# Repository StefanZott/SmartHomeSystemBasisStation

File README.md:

# SmartHomeSystemBasisStation

## Kurzbeschreibung

SmartHome-Basisstation auf Basis des **ESP32-S3** mit eigener Platine, ESP-IDF-Firmware und Web-Oberfläche zur WLAN-Konfiguration und Gerätediagnose. Das Repository bündelt Hardware (KiCad), Firmware und SPIFFS-Web-Assets in einem Projekt.

## Architektur-Überblick

| Pfad | Inhalt |
|------|--------|
| `main/` | Firmware (ESP-IDF), Einstieg `main.c` |
| `spiffs/` | Web-UI (HTML, CSS, JS) → SPIFFS-Image |
| `pcb/` | KiCad-Schaltplan und Layout der Basisstation |
| `docs/` | Projektdokumentation und Anwenderdoku |

Stückliste und Pinout: [docs/project/hardware.md](docs/project/hardware.md)

## Toolchain

- **Firmware:** [ESP-IDF](https://docs.espressif.com/projects/esp-idf/) **v5.5.2** für ESP32-S3, Build über `idf.py`
- **IDE:** VS Code mit ESP-IDF-Erweiterung; optional Dev Container (`.devcontainer/`)
- **Hardware:** KiCad 8/9 — Projekt unter `pcb/BasisStation/`

## Deep Dive

Technische Architektur, Module, Startablauf und Verzeichnisstruktur:

→ [docs/project/architecture.md](docs/project/architecture.md)

Weitere Themen: [Kommunikation](docs/project/communication.md) · [Sicherheit](docs/project/security.md) · [Speicher-Layout](docs/project/memory_map.md)

## Deployment

Build, Flash und Monitor (Kurzfassung):

```text
idf.py set-target esp32s3
idf.py build
idf.py flash monitor
```

Ausführliche Anleitung, Partitionierung und Voraussetzungen:

→ [docs/project/architecture.md#deployment](docs/project/architecture.md#deployment)

## Release & Tags

Aktuelle Firmware-Version: siehe Datei [`version`](version) (Format `X.XX.XXX`, derzeit `0.00.001`).

| Tag (Beispiel) | Bedeutung |
|----------------|-----------|
| `v0.00.001` | Veröffentlichte bzw. testbare Firmware-Version |
| `release` | Marker für den aktuellen Release-Stand im Repository |

Kundenspezifische Builds: `v0.00.005-kundexyz`. Details: [docs/userdoc/git_guidelines.md](docs/userdoc/git_guidelines.md).

Agenten-Regeln und Workflow: [CLAUDE.md](CLAUDE.md)

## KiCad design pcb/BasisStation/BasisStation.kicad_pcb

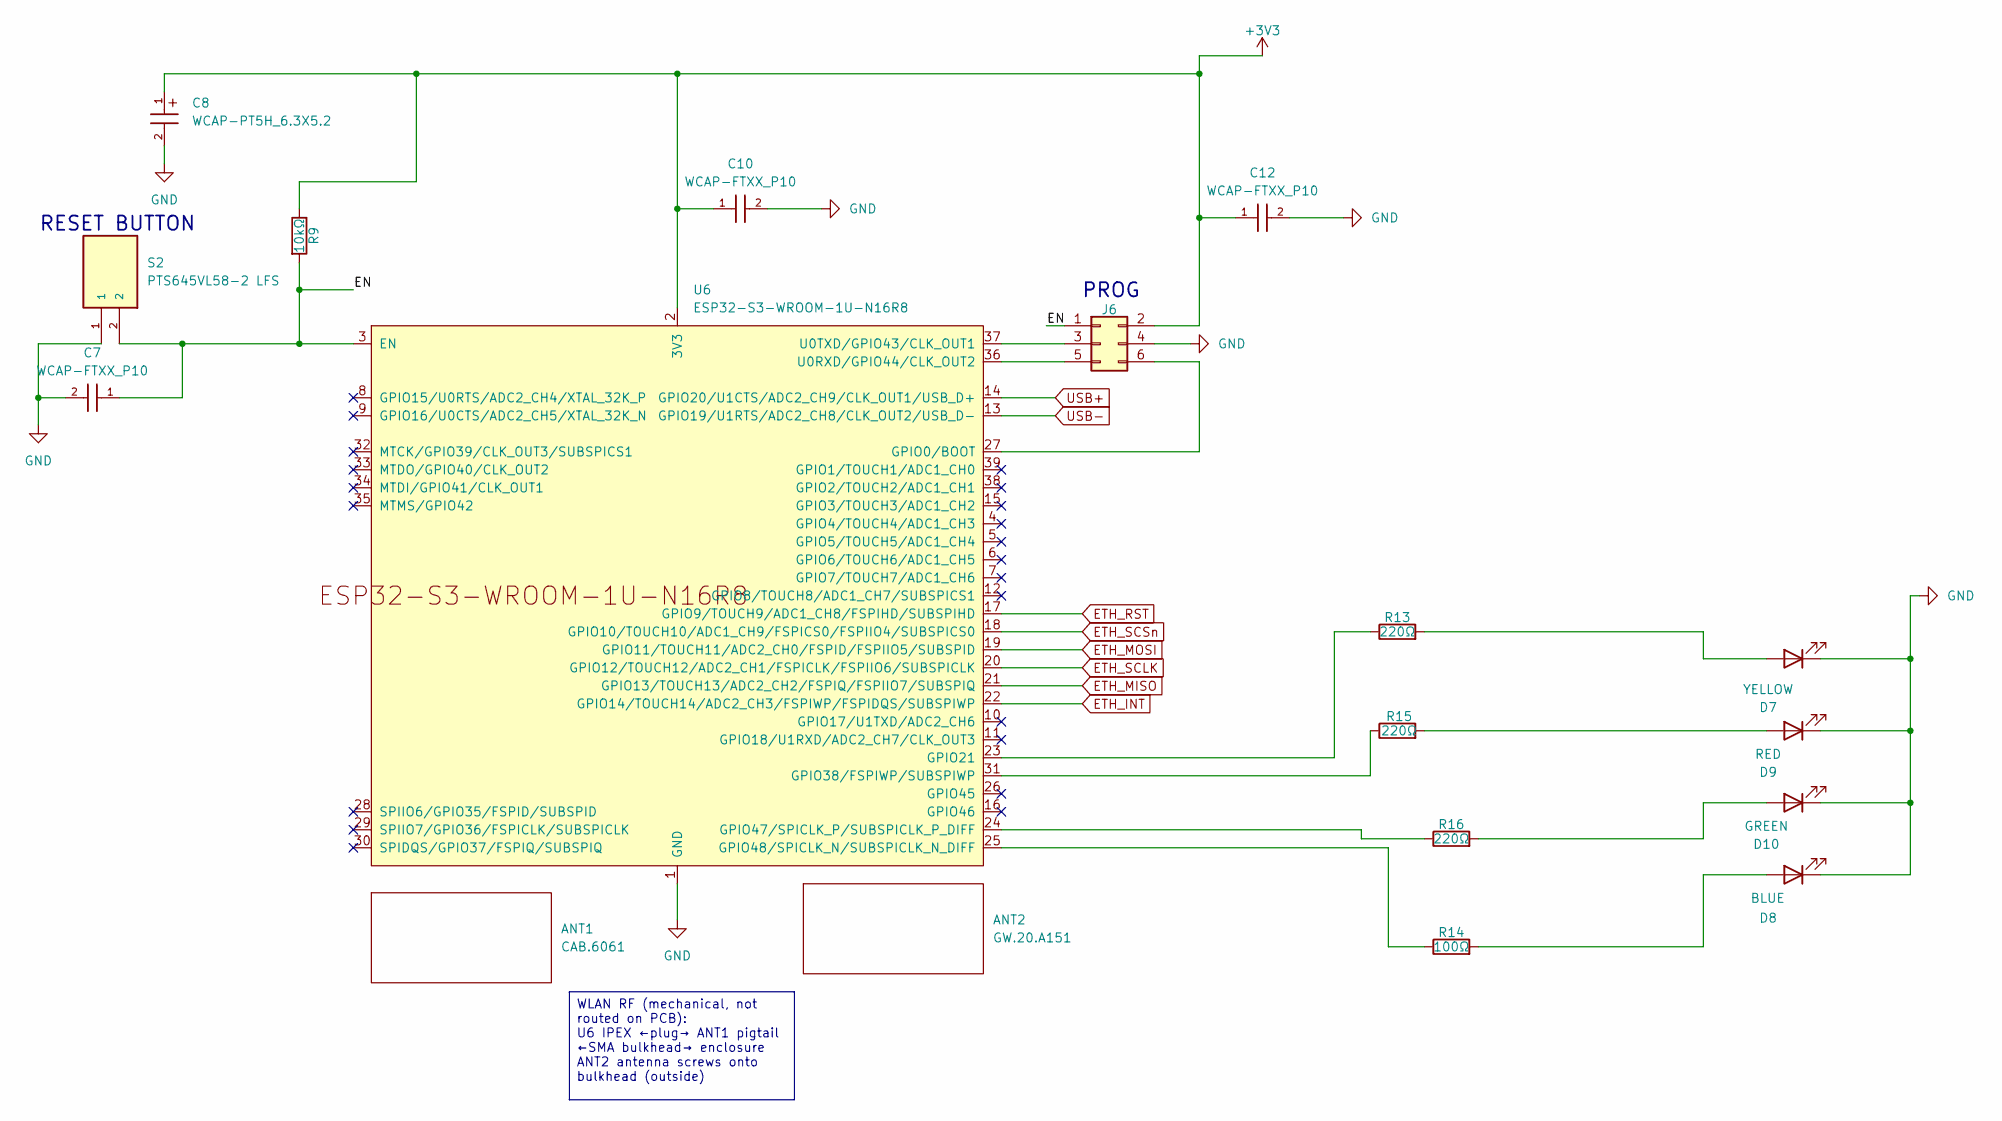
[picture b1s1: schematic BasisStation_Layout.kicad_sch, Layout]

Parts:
ANT1: CAB.6061; Manufacturer_Part_Number CAB.6061; Mouser Part Number 960-CAB.6061
ANT2: GW.20.A151; Manufacturer_Part_Number GW.20.A151; Mouser Part Number 960-GW.20.A151
C7, C10, C12: WCAP-FTXX_P10; WCAP-FTXX_P10L13W7H13
C8: WCAP-PT5H_6.3X5.2; WCAP-PT5H_6.3X5.2_DXL_
D7: YELLOW; LED_D3.0mm_Horizontal_O1.27mm_Z2.0mm
D8: BLUE; LED_D3.0mm_Horizontal_O1.27mm_Z2.0mm; Manufacturer_Part_Number 151033BS03000; Mouser Part Number 710-151033BS03000
D9: RED; LED_D3.0mm_Horizontal_O1.27mm_Z2.0mm; Manufacturer_Part_Number 151033RS03000; Mouser Part Number 710-151033RS03000
D10: GREEN; LED_D3.0mm_Horizontal_O1.27mm_Z2.0mm; Manufacturer_Part_Number 151031VS06000; Mouser Part Number 710-151031VS06000
J6: 61200621621; Manufacturer_Part_Number 61200621621; Mouser Part Number 710-61200621621
R9: 10kΩ; R_0805_2012Metric; Manufacturer_Part_Number RC0805FR-0710KL; Mouser Part Number 603-RC0805FR-0710KL
R13, R15, R16: 220Ω; R_0805_2012Metric; Manufacturer_Part_Number RC0805FR-07220RL; Mouser Part Number 603-RC0805FR-07220RL
R14: 100Ω; R_0805_2012Metric; Manufacturer_Part_Number RC0805FR-07100RL; Mouser Part Number 603-RC0805FR-07100RL
S2: PTS645VL58-2 LFS; SW_Tactile_SPST_Angled_PTS645Vx58-2LFS; MOUSER_PART_NUMBER 611-PTS645VL582
U6: ESP32-S3-WROOM-1U-N16R8; ESP32-S3-WROOM-1U; Mouser Part Number 356-ESP32S3WM1UN16R8

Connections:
+3V3: C8.1, C10.1, C12.1, J6.2, R9.1, U6.2 (3V3); also elsewhere on the board
/Layout/EN: C7.1, J6.1, R9.2, S2.2, U6.3 (EN)
ETH_INT: U6.22 (GPIO14/TOUCH14/ADC2_CH3/FSPIWP/FSPIDQS/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); also elsewhere on the board
ETH_MISO: U6.21 (GPIO13/TOUCH13/ADC2_CH2/FSPIQ/FSPIIO7/S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); also elsewhere on the board
ETH_MOSI: U6.19 (GPIO11/TOUCH11/ADC2_CH0/FSPID/FSPIIO5/S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); also elsewhere on the board
ETH_RST: U6.17 (GPIO9/TOUCH9/ADC1_CH8/FSPIHD/SUBSPIHD); also elsewhere on the board
ETH_SCLK: U6.20 (GPIO12/TOUCH12/ADC2_CH1/FSPICLK/FSPIIO6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); also elsewhere on the board
ETH_SCSn: U6.18 (GPIO10/TOUCH10/ADC1_CH9/FSPICS0/FSPIIO4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); also elsewhere on the board
GND: C7.2, C8.2, C10.2, C12.2, D7.1 (K), D8.1 (K), D9.1 (K), D10.1 (K), J6.4, S2.1, U6.1 (GND), U6.40 (GND), U6.41 (GND); also elsewhere on the board
unnamed: D7.2 (A), R13.2
unnamed: D8.2 (A), R14.2
unnamed: D9.2 (A), R15.2
unnamed: D10.2 (A), R16.2
unnamed: J6.3, U6.37 (U0TXD/GPIO43/CLK_OUT1)
unnamed: J6.5, U6.36 (U0RXD/GPIO44/CLK_OUT2)
unnamed: J6.6, U6.27 (GPIO0/BOOT)
unnamed: R13.1, U6.23 (GPIO21)
unnamed: R15.1, U6.31 (GPIO38/FSPIWP/SUBSPIWP)
unnamed: R16.1, U6.24 (GPIO47/SPICLK_P/SUBSPICLK_P_DIFF)
unnamed: R14.1, U6.25 (GPIO48/SPICLK_N/SUBSPICLK_N_DIFF)
USB+: U6.14 (GPIO20/U1CTS/ADC2_CH9/CLK_OUT1/USB_D+); also elsewhere on the board
USB-: U6.13 (GPIO19/U1RTS/ADC2_CH8/CLK_OUT2/USB_D-); also elsewhere on the board

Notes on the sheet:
RESET BUTTON
PROG
WLAN RF (mechanical, not routed on PCB): U6 IPEX ←plug→ ANT1 pigtail ←SMA bulkhead→ enclosure ANT2 antenna screws onto bulkhead (outside)

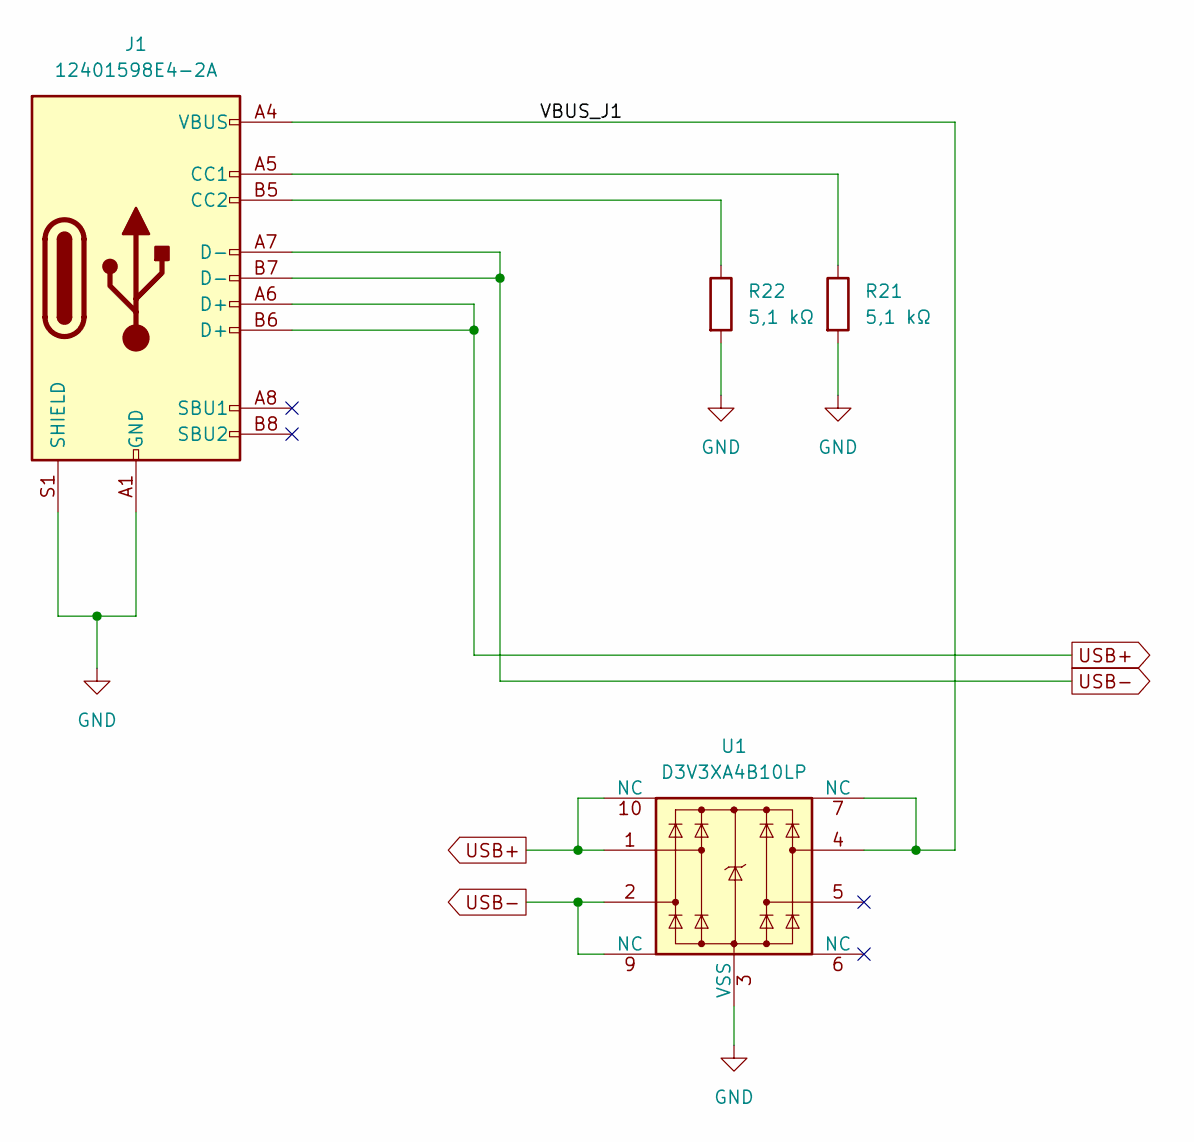
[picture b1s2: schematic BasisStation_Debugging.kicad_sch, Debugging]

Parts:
J1: 12401598E4-2A; USB_C_Receptacle_Amphenol_12401598E4-2A; Manufacturer_Part_Number 12401598E4#2A; Mouser Part Number 523-12401598E4#2A
R21, R22: 5,1 kΩ; R_0805_2012Metric; Manufacturer_Part_Number RC0805FR-075K1L; Mouser Part Number 603-RC0805FR-075K1L
U1: D3V3XA4B10LP; Diodes_UDFN-10_1x2.5mm_P0.5mm; Manufacturer_Part_Number D3V3XA4B10LP-7; Mouser Part Number 621-D3V3XA4B10LP-7

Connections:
/Debugging/VBUS_J1: J1.A4 (VBUS), J1.A9 (VBUS), J1.B4 (VBUS), J1.B9 (VBUS), U1.4, U1.7 (NC)
GND: J1.A1 (GND), J1.A12 (GND), J1.B1 (GND), J1.B12 (GND), J1.S1 (SHIELD), R21.2, R22.2, U1.3 (VSS), U1.8 (VSS); also elsewhere on the board
unnamed: J1.A5 (CC1), R21.1
unnamed: J1.B5 (CC2), R22.1
USB+: J1.A6 (D+), J1.B6 (D+), U1.1, U1.10 (NC); also elsewhere on the board
USB-: J1.A7 (D-), J1.B7 (D-), U1.2, U1.9 (NC); also elsewhere on the board

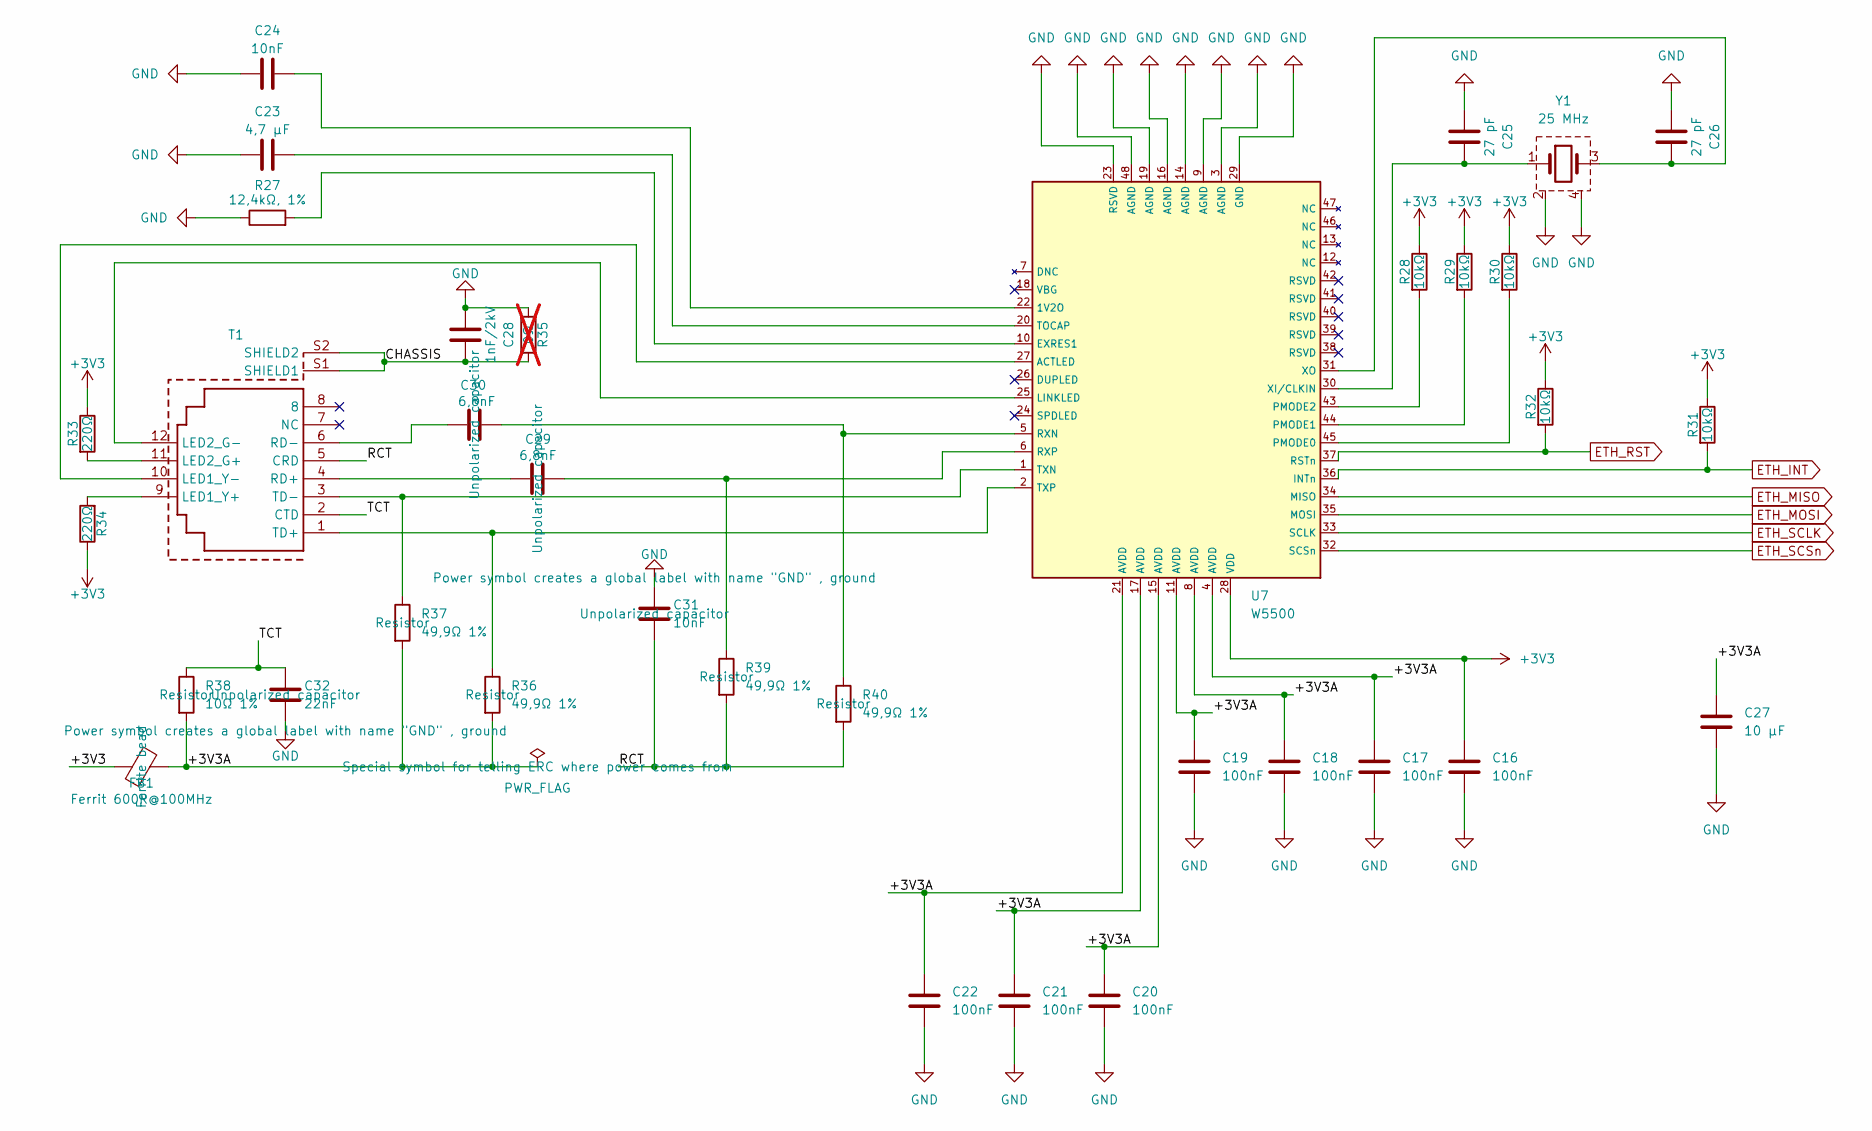
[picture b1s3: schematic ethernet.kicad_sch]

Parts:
C16, C17, C18, C19, C20, C21, C22: 100nF; C_0805_2012Metric; Manufacturer_Part_Number CC0805KRX7R9BB104; Mouser Part Number 603-CC805KRX7R9BB104
C23: 4,7 µF; C_0805_2012Metric; Manufacturer_Part_Number CL21A475KAQNNNE; Mouser Part Number 187-CL21A475KAQNNNE
C24, C31: 10nF; C_0805_2012Metric; Manufacturer_Part_Number CC0805KRX7R9BB103; Mouser Part Number 603-CC805KRX7R9BB103
C25, C26: 27 pF; C_0805_2012Metric; Manufacturer_Part_Number CC0805JRNPO9BN270; Mouser Part Number 603-CC805JRNPO9BN270
C27: 10 µF; C_0805_2012Metric; Manufacturer_Part_Number CL21B106KOQNNNE; Mouser Part Number 187-CL21B106KOQNNNE
C28: 1nF/2kV; C_1206_3216Metric; Manufacturer_Part_Number C1206C102KGRACTU; Mouser Part Number 80-C1206C102KGR
C29, C30: 6,8nF; C_0805_2012Metric; Manufacturer_Part_Number CC0805KRX7R9BB682; Mouser Part Number 603-CC805KRX7R9BB682
C32: 22nF; C_0805_2012Metric; Manufacturer_Part_Number CL21B223KBANNNC; Mouser Part Number 187-CL21B223KBANNNC
FB1: Ferrit 600R@100MHz; L_0805_2012Metric; Manufacturer_Part_Number BLM21PG601SN1D; Mouser Part Number 81-BLM21PG601SN1D
R27: 12,4kΩ, 1%; R_0805_2012Metric; Manufacturer_Part_Number RC0805FR-0712K4L; Mouser Part Number 603-RC0805FR-0712K4L
R28, R29, R30, R31, R32: 10kΩ; R_0805_2012Metric; Manufacturer_Part_Number RC0805FR-0710KL; Mouser Part Number 603-RC0805FR-0710KL
R33, R34: 220Ω; R_0805_2012Metric; Manufacturer_Part_Number RC0805FR-07220RL; Mouser Part Number 603-RC0805FR-07220RL
R35: 0Ω; R_0805_2012Metric; Manufacturer_Part_Number RC0805JR-070RL; Mouser Part Number 603-RC0805JR-070RL; not fitted
R36, R37, R39, R40: 49,9Ω 1%; R_0805_2012Metric; Manufacturer_Part_Number RC0805FR-0749R9L; Mouser Part Number 603-RC0805FR-0749R9L
R38: 10Ω 1%; R_0805_2012Metric; Manufacturer_Part_Number RC0805FR-0710RL; Mouser Part Number 603-RC0805FR-0710RL
T1: 7499011121A; T_Wurth_WE-RJ45LAN_7499011121A; Part Number 7499011121A; Mouser Part Number 710-7499011121A
U7: W5500; 48LQFP_W5500_WIZ; Manufacturer_Part_Number W5500
Y1: 25 MHz; Y_Wurth_WE-XTAL_Quartz-CFPX-104; Part Number 830059532; Mouser Part Number 710-830059532

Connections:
+3V3: C16.1, FB1.1, R28.1, R29.1, R30.1, R31.1, R32.1, R33.1, R34.1, U7.28 (VDD); also elsewhere on the board
/Ethernet/+3V3A: C17.1, C18.1, C19.1, C20.1, C21.1, C22.1, C27.1, FB1.2, R36.2, R37.2, R38.2, U7.4 (AVDD), U7.8 (AVDD), U7.11 (AVDD), U7.15 (AVDD), U7.17 (AVDD), U7.21 (AVDD)
/Ethernet/CHASSIS: C28.2, R35.1, T1.S1 (SHIELD1), T1.S2 (SHIELD2)
/Ethernet/RCT: C31.2, R39.2, R40.2, T1.5 (CRD)
/Ethernet/TCT: C32.1, R38.1, T1.2 (CTD)
ETH_INT: R31.2, U7.36 (INTn); also elsewhere on the board
ETH_MISO: U7.34 (MISO); also elsewhere on the board
ETH_MOSI: U7.35 (MOSI); also elsewhere on the board
ETH_RST: R32.2, U7.37 (RSTn); also elsewhere on the board
ETH_SCLK: U7.33 (SCLK); also elsewhere on the board
ETH_SCSn: U7.32 (SCSn); also elsewhere on the board
GND: C16.2, C17.2, C18.2, C19.2, C20.2, C21.2, C22.2, C23.1, C24.1, C25.1, C26.1, C27.2, C28.1, C31.1, C32.2, R27.1, R35.2, U7.3 (AGND), U7.9 (AGND), U7.14 (AGND), U7.16 (AGND), U7.19 (AGND), U7.23 (RSVD), U7.29 (GND), U7.48 (AGND), Y1.2 (GND), Y1.4 (GND1); also elsewhere on the board
unnamed: R34.2, T1.9 (LED1_Y+)
unnamed: T1.10 (LED1_Y-), U7.27 (ACTLED)
unnamed: R33.2, T1.11 (LED2_G+)
unnamed: T1.12 (LED2_G-), U7.25 (LINKLED)
unnamed: C29.1, T1.4 (RD+)
unnamed: C30.1, T1.6 (RD-)
unnamed: R36.1, T1.1 (TD+), U7.2 (TXP)
unnamed: R37.1, T1.3 (TD-), U7.1 (TXN)
unnamed: C24.2, U7.22 (1V2O)
unnamed: R27.2, U7.10 (EXRES1)
unnamed: R30.2, U7.45 (PMODE0)
unnamed: R29.2, U7.44 (PMODE1)
unnamed: R28.2, U7.43 (PMODE2)
unnamed: C30.2, R40.1, U7.5 (RXN)
unnamed: C29.2, R39.1, U7.6 (RXP)
unnamed: C23.2, U7.20 (TOCAP)
unnamed: C25.2, U7.30 (XI/CLKIN), Y1.1
unnamed: C26.2, U7.31 (XO), Y1.3

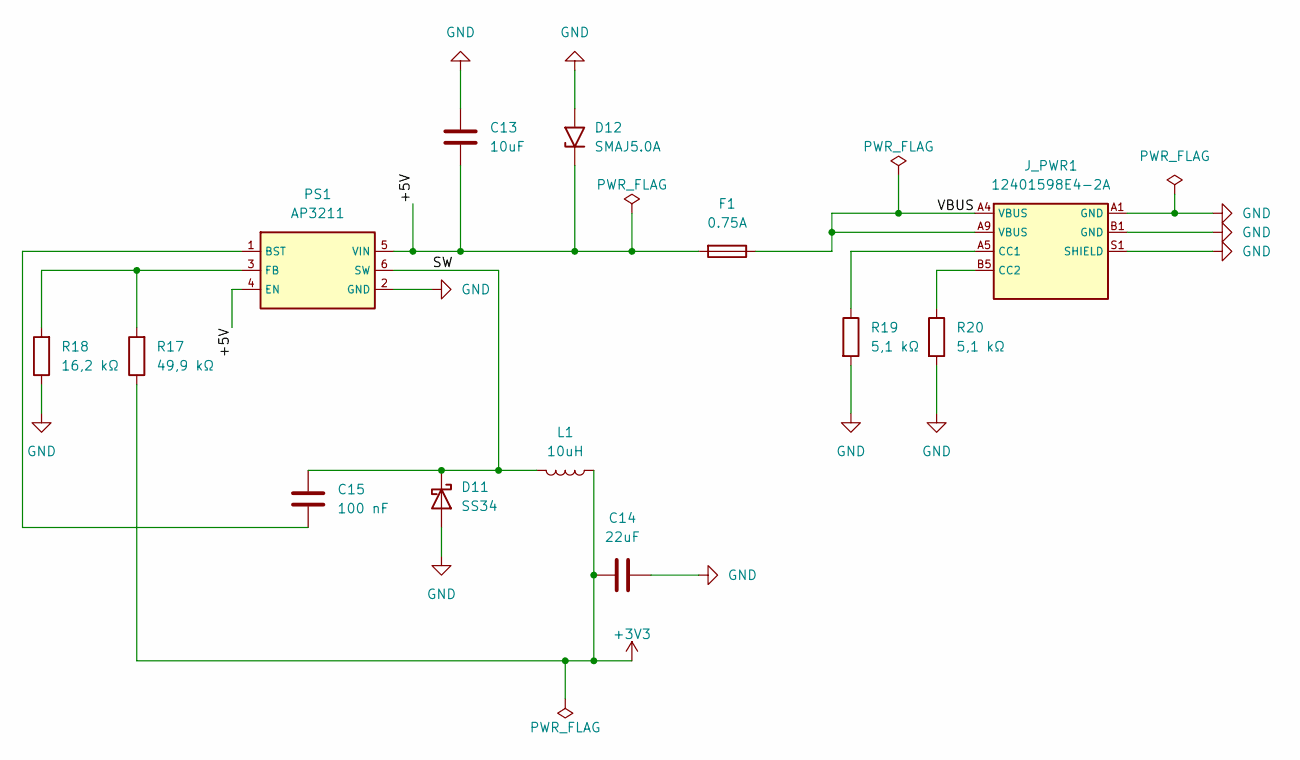
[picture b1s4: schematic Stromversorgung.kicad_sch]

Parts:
C13: 10uF; C_0805_2012Metric; Manufacturer_Part_Number CL21B106KOQNNNE; Mouser Part Number 187-CL21B106KOQNNNE
C14: 22uF; C_0805_2012Metric; Manufacturer_Part_Number CL21A226MOQNNNE; Mouser Part Number 187-CL21A226MOQNNNE
C15: 100 nF; C_0805_2012Metric; Manufacturer_Part_Number CC0805KRX7R9BB104; Mouser Part Number 603-CC805KRX7R9BB104
D11: SS34; D_SMA; Manufacturer_Part_Number SS34-HF; Mouser Part Number 750-SS34-HF
D12: SMAJ5.0A; D_SMA; Manufacturer_Part_Number SMAJ5.0A; Mouser Part Number 576-SMAJ5.0A
F1: 0.75A; Fuse_1206_3216Metric; Manufacturer_Part_Number 1206L075/16WR; Mouser Part Number 576-1206L075/16WR
J_PWR1: 12401598E4-2A; USB_C_Receptacle_Amphenol_12401598E4-2A; Manufacturer_Part_Number 12401598E4#2A; Mouser Part Number 523-12401598E4#2A
L1: 10uH; L_Bourns_SRN6045TA; Manufacturer_Part_Number SRN6045TA-100M; Mouser Part Number 652-SRN6045TA-100M
PS1: AP3211; MP2359DJ; Manufacturer_Part_Number AP3211KTR-G1; Mouser Part Number 621-AP3211KTR-G1
R17: 49,9 kΩ; R_0805_2012Metric; Manufacturer_Part_Number RC0805FR-0749K9L; Mouser Part Number 603-RC0805FR-0749K9L
R18: 16,2 kΩ; R_0805_2012Metric; Manufacturer_Part_Number RC0805FR-0716K2L; Mouser Part Number 603-RC0805FR-0716K2L
R19, R20: 5,1 kΩ; R_0805_2012Metric; Manufacturer_Part_Number RC0805FR-075K1L; Mouser Part Number 603-RC0805FR-075K1L

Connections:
+3V3: C14.2, L1.1, R17.1; also elsewhere on the board
/Stromversorgung/+5V: C13.2, D12.1 (A1), F1.2, PS1.4 (EN), PS1.5 (VIN)
/Stromversorgung/SW: C15.2, D11.1 (K), L1.2, PS1.6 (SW)
/Stromversorgung/VBUS: F1.1, J_PWR1.A4 (VBUS), J_PWR1.A9 (VBUS), J_PWR1.B4 (VBUS), J_PWR1.B9 (VBUS)
GND: C13.1, C14.1, D11.2 (A), D12.2 (A2), J_PWR1.A1 (GND), J_PWR1.A12 (GND), J_PWR1.B1 (GND), J_PWR1.B12 (GND), J_PWR1.S1 (SHIELD), PS1.2 (GND), R18.1, R19.2, R20.2; also elsewhere on the board
unnamed: J_PWR1.A5 (CC1), R19.1
unnamed: J_PWR1.B5 (CC2), R20.1
unnamed: C15.1, PS1.1 (BST)
unnamed: PS1.3 (FB), R17.2, R18.2

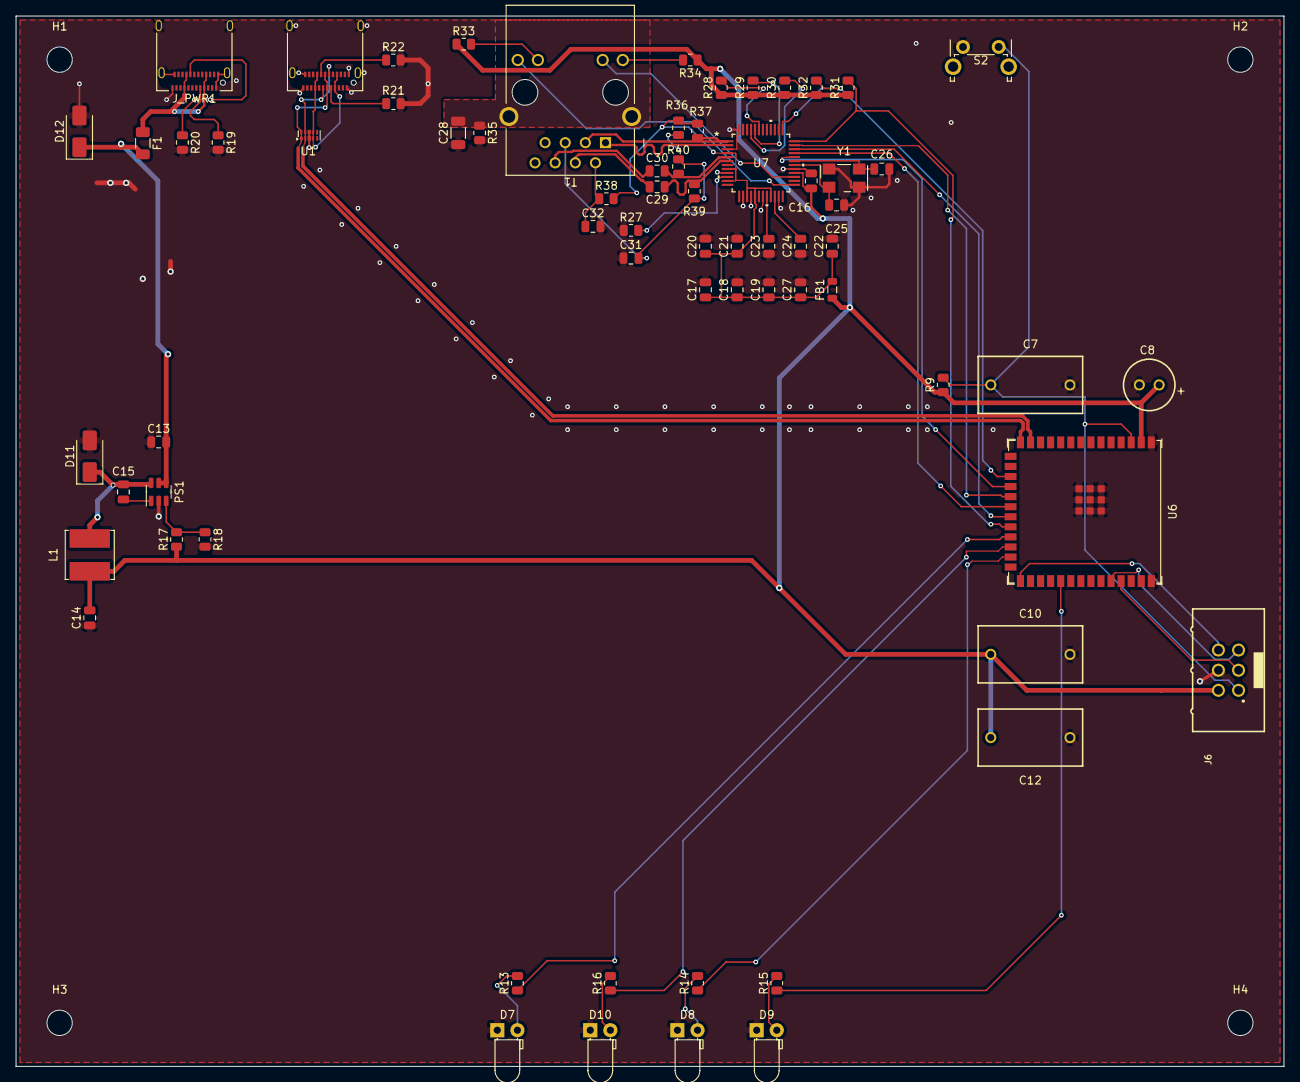
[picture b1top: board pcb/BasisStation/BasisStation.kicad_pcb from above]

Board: 2 copper layers, 160.0 x 132.6 mm, 72 parts (0 on the bottom side), 54 nets.

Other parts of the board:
H1, H2, H3, H4: MountingHole_3.2mm_M3

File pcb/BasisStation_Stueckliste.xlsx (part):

Stückliste SmartHome-Basisstation
Quelle: pcb/BasisStation/*.kicad_sch · Stand 2026-09-30 · 41 Positionen · 70 Ba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
Grün = Preis aus Mouser- bzw. DigiKey-API (Tagespreis, unverbindlich, Staffel p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
Pos | Menge | Referenzen | Wert (Schaltplan) | Technik | Footprint | Hersteller | Hersteller-Teilenr. | Mouser-Teilenr. | Mouser EUR | Mouser Lager | DigiKey-Teilenr. | DigiKey EUR | DigiKey Lager | Lebenszyklus | Bezugsquelle | Einzelpreis EUR | Gesamtpreis EUR | Mouser | DigiKey | Datenblatt | Status | Hinweis
1 | 1 | ANT1 | CAB.6061 |  |  | Taoglas | CAB.6061 | 960-CAB.6061 | 4.47 | 845 | 931-CAB.6061-ND | 4.45 | 897 | New Product | DigiKey |  |  | Mouser | DigiKey | PDF | eindeutig
2 | 1 | ANT2 | GW.20.A151 |  |  | Taoglas | GW.20.A151 | 960-GW.20.A151 | 8.460000000000001 | 650 | 931-GW.20.A151-ND | 8.42 | 59 | Aktiv | DigiKey |  |  | Mouser | DigiKey | PDF | eindeutig
3 | 3 | C7, C10, C12 | WCAP-FTXX_P10 | SMD | WCAP-FTXX_P10:WCAP-FTXX_P10L13W7H13 | Würth Elektronik | 890334023023 | 710-890334023023 | 0.353 | 1350 | 732-5833-ND | 0.35 | 2491 | Aktiv | DigiKey |  |  | Mouser | DigiKey | PDF | eindeutig
4 | 1 | C8 | WCAP-PT5H_6.3X5.2 | SMD | WCAP-PT5H_6.3X5.2:WCAP-PT5H_6.3X5.2_DXL_ | Wurth Elektronik | 870235673001 | 710-870235673001 | 1.36 | 2394 | 732-870235673001CT-ND | 1.35 | 1017 | Aktiv | DigiKey |  |  | Mouser | DigiKey | PDF | eindeutig
5 | 2 | C13, C27 | 10uF | SMD | Capacitor_SMD:C_0805_2012Metric | Samsung | CL21B106KOQNNNE | 187-CL21B106KOQNNNE | 0.421 | 323680 | 1276-2872-1-ND | 0.24 | 277103 | Aktiv | DigiKey |  |  | Mouser | DigiKey | PDF | eindeutig
6 | 1 | C14 | 22uF | SMD | Capacitor_SMD:C_0805_2012Metric | Samsung | CL21A226MOQNNNE | 187-CL21A226MOQNNNE | 0.55 | 2519 | 1276-2909-1-ND | 0.27 | 25218 | Aktiv | DigiKey |  |  | Mouser | DigiKey | PDF | eindeutig
7 | 8 | C15, C16, C17, C18, C19, C20, C21, C22 | 100 nF | SMD | Capacitor_SMD:C_0805_2012Metric | YAGEO | CC0805KRX7R9BB104 | 603-CC805KRX7R9BB104 | 0.12 | 1217786 | 311-1140-1-ND | 0.15 | 1635243 | Aktiv | Mouser |  |  | Mouser | DigiKey | PDF | eindeutig
8 | 1 | C23 | 4,7 µF | SMD | Capacitor_SMD:C_0805_2012Metric | Samsung | CL21A475KAQNNNE | 187-CL21A475KAQNNNE | 0.138 | 201 | 1276-1244-1-ND | 0.11 | 0 | Aktiv | Mouser |  |  | Mouser | DigiKey | PDF | eindeutig | Bei DigiKey nicht ausreichend ab Lager (0) — nur über Mouser.
9 | 2 | C24, C31 | 10nF | SMD | Capacitor_SMD:C_0805_2012Metric | YAGEO | CC0805KRX7R9BB103 | 603-CC805KRX7R9BB103 | 0.146 | 358983 | 311-1136-1-ND | 0.12 | 234857 | Aktiv | DigiKey |  |  | Mouser | DigiKey | PDF | eindeutig
10 | 2 | C25, C26 | 27 pF | SMD | Capacitor_SMD:C_0805_2012Metric | YAGEO | CC0805JRNPO9BN270 | 603-CC805JRNPO9BN270 | 0.103 | 40719 | 311-1104-1-ND | 0.14 | 0 | Aktiv | Mouser |  |  | Mouser | DigiKey | PDF | eindeutig | Bei DigiKey nicht ausreichend ab Lager (0) — nur über Mouser.
11 | 1 | C28 | 1nF/2kV | SMD | Capacitor_SMD:C_1206_3216Metric | KEMET | C1206C102KGRACTU | 80-C1206C102KGR | 1.33 | 196492 | 399-C1206C102KGRACTUCT-ND | 1.33 | 605024 | Aktiv | DigiKey |  |  | Mouser | DigiKey | PDF | eindeutig
12 | 2 | C29, C30 | 6,8nF | SMD | Capacitor_SMD:C_0805_2012Metric | YAGEO | CC0805KRX7R9BB682 | 603-CC805KRX7R9BB682 | 0.112 | 23242 | 311-1135-1-ND | 0.12 | 1630 | Aktiv | Mouser |  |  | Mouser | DigiKey | PDF | eindeutig
13 | 1 | C32 | 22nF | SMD | Capacitor_SMD:C_0805_2012Metric | Samsung | CL21B223KBANNNC | 187-CL21B223KBANNNC | 0.138 | 3047 | 1276-1081-1-ND | 0.09 | 9435 | Aktiv | DigiKey |  |  | Mouser | DigiKey | PDF | eindeutig
14 | 1 | D7 | YELLOW | SMD | LED_THT:LED_D3.0mm_Horizontal_O1.27mm_Z2.0mm | Wurth Electronics | 151031YS05900 | 710-151031YS05900 | 0.146 | 1693 | 732-5009-ND | 0.15 | 3781 | Aktiv | Mouser |  |  | Mouser | DigiKey | PDF | eindeutig
15 | 1 | D8 | BLUE | SMD | LED_THT:LED_D3.0mm_Horizontal_O1.27mm_Z2.0mm | Würth Elektronik | 151033BS03000 | 710-151033BS03000 | 0.232 | 7884 | 732-5011-ND | 0.22 | 9093 | Aktiv | DigiKey |  |  | Mouser | DigiKey | PDF | eindeutig
16 | 1 | D9 | RED | SMD | LED_THT:LED_D3.0mm_Horizontal_O1.27mm_Z2.0mm | Würth Elektronik | 151033RS03000 | 710-151033RS03000 | 0.146 | 34357 | 732-5013-ND | 0.15 | 57977 | Aktiv | Mouser |  |  | Mouser | DigiKey | PDF | eindeutig
17 | 1 | D10 | GREEN | SMD | LED_THT:LED_D3.0mm_Horizontal_O1.27mm_Z2.0mm | Würth Elektronik | 151031VS06000 | 710-151031VS06000 | 0.138 | 23526 | 732-5008-ND | 0.14 | 53301 | Aktiv | Mouser |  |  | Mouser | DigiKey | PDF | eindeutig
18 | 1 | D11 | SS34 | SMD | Diode_SMD:D_SMA | Comchip Technology | SS34-HF | 750-SS34-HF | 0.464 | 22099 | 641-2115-1-ND | 0.46 | 53701 | Aktiv | DigiKey |  |  | Mouser | DigiKey | PDF | eindeutig
19 | 1 | D12 | SMAJ5.0A | SMD | Diode_SMD:D_SMA | Littelfuse | SMAJ5.0A | 576-SMAJ5.0A | 0.378 | 24423 | SMAJ5.0ALFCT-ND | 0.43 | 167714 | Aktiv | Mouser |  |  | Mouser | DigiKey | PDF | eindeutig
20 | 1 | F1 | 1.1A | SMD | Fuse:Fuse_1206_3216Metric | Bourns | MF-NSMF110-2 | 652-MF-NSMF110-2 | 0.275 | 11988 | MF-NSMF110-2CT-ND | 0.33 | 41044 | Aktiv | Mouser |  |  | Mouser | DigiKey | PDF | eindeutig
21 | 1 | FB1 | Ferrit 600R@100MHz | SMD | Inductor_SMD:L_0805_2012Metric | Murata | BLM21PG601SN1D | 81-BLM21PG601SN1D | 0.103 | 0 | 490-BLM21PG601SN1DCT-ND | 0.1 | 4446 | Aktiv | DigiKey |  |  | Mouser | DigiKey | PDF | eindeutig | Bei Mouser nicht ausreichend ab Lager (0) — nur über DigiKey.
22 | 2 | J1, J_PWR1 | 12401598E4-2A | THT | shbs_power:USB_C_Receptacle_Amphenol_12401598E4-2A | Amphenol | 12401598E4#2A | 523-12401598E4#2A | 1.62 | 9245 | 12401598E4#2ACT-ND | 1.64 | 39568 | Aktiv | Mouser |  |  | Mouser | DigiKey | PDF | eindeutig
23 | 1 | J6 | 61200621621 | THT | wuerth_6120XX21621:61200621621 | Würth Elektronik | 61200621621 | 710-61200621621 | 0.404 | 46778 | 732-5394-ND | 0.43 | 20950 | Aktiv | Mouser |  |  | Mouser | DigiKey | PDF | eindeutig
24 | 1 | L1 | 10uH | SMD | Inductor_SMD:L_Bourns_SRN6045TA | Bourns | SRN6045TA-100M | 652-SRN6045TA-100M | 0.43 | 4297 | SRN6045TA-100MCT-ND | 0.43 | 4355 | Aktiv | DigiKey |  |  | Mouser | DigiKey | PDF | eindeutig
25 | 1 | PS1 | AP3211 | SMD | shbs_power:MP2359DJ | Diodes Incorporated | AP3211KTR-G1 | 621-AP3211KTR-G1 | 0.464 | 18260 | AP3211KTR-G1DICT-ND | 0.47 | 32678 | Aktiv | Mouser |  |  | Mouser | DigiKey | PDF | eindeutig
26 | 6 | R9, R28, R29, R30, R31, R32 | 10kΩ | SMD | Resistor_SMD:R_0805_2012Metric | YAGEO | RC0805FR-0710KL | 603-RC0805FR-0710KL | 0.08599999999999999 | 3453672 | 311-10.0KCRCT-ND | 0.09 | 1935589 | Aktiv | Mouser |  |  | Mouser | DigiKey | PDF | eindeutig
27 | 5 | R13, R15, R16, R33, R34 | 220Ω | SMD | Resistor_SMD:R_0805_2012Metric | YAGEO | RC0805FR-07220RL | 603-RC0805FR-07220RL | 0.08599999999999999 | 218894 | 311-220CRCT-ND | 0.09 | 380504 | Aktiv | Mouser |  |  | Mouser | DigiKey | PDF | eindeutig
28 | 1 | R14 | 100Ω | SMD | Resistor_SMD:R_0805_2012Metric | YAGEO | RC0805FR-07100RL | 603-RC0805FR-07100RL | 0.08599999999999999 | 471173 | 311-100CRCT-ND | 0.09 | 1407631 | Aktiv | Mouser |  |  | Mouser | DigiKey | PDF | eindeutig
29 | 1 | R17 | 49,9 kΩ | SMD | Resistor_SMD:R_0805_2012Metric | YAGEO | RC0805FR-0749K9L | 603-RC0805FR-0749K9L | 0.08599999999999999 | 195715 | 311-49.9KCRCT-ND | 0.09 | 950283 | Aktiv | Mouser |  |  | Mouser | DigiKey | PDF | eindeutig
30 | 1 | R18 | 16,2 kΩ | SMD | Resistor_SMD:R_0805_2012Metric | YAGEO | RC0805FR-0716K2L | 603-RC0805FR-0716K2L | 0.08599999999999999 | 12535 | 311-16.2KCRCT-ND | 0.09 | 38373 | Aktiv | Mouser |  |  | Mouser | DigiKey | PDF | eindeutig
31 | 4 | R19, R20, R21, R22 | 5,1 kΩ | SMD | Resistor_SMD:R_0805_2012Metric | YAGEO | RC0805FR-075K1L | 603-RC0805FR-075K1L | 0.103 | 36518 | 311-5.10KCRCT-ND | 0.09 | 0 | Aktiv | Mouser |  |  | Mouser | DigiKey | PDF | eindeutig | Bei DigiKey nicht ausreichend ab Lager (0) — nur über Mouser.
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
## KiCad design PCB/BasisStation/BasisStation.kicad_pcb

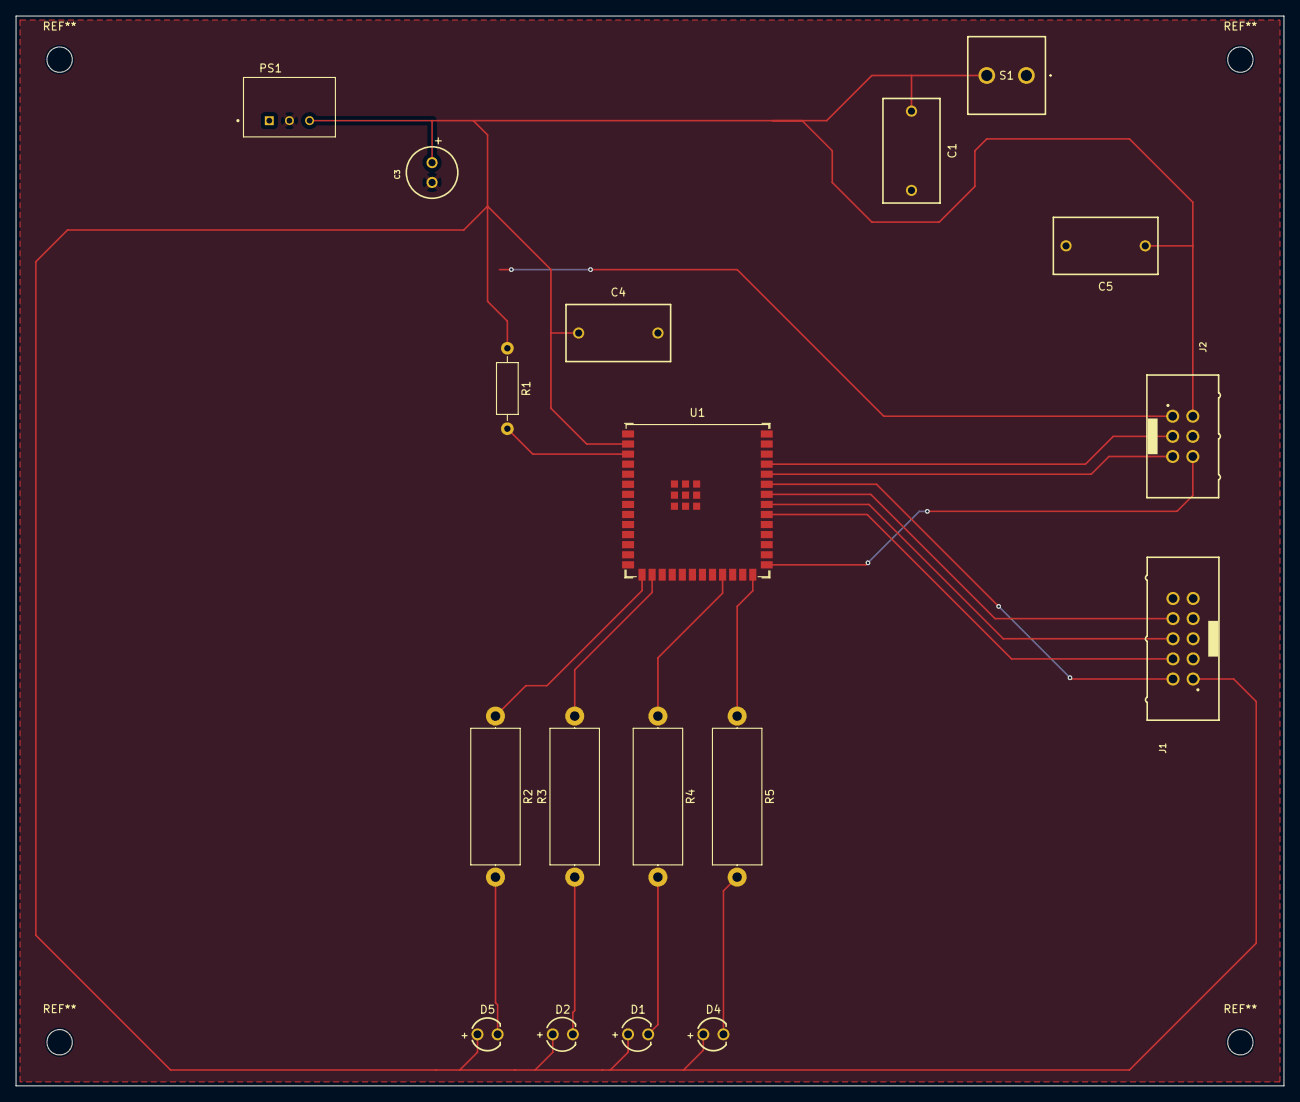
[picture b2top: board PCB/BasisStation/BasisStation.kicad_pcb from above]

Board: 2 copper layers, 160.0 x 135.0 mm, 18 parts (0 on the bottom side), 18 nets.

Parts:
C1, C4, C5: WCAP-FTXX_P10; WCAP-FTXX_P10L13W7H13
C3: WCAP-PT5H_6.3X5.2; WCAP-PT5H_6.3X5.2_DXL_
D1: RED; WL-TMRW_3MM
D2: BLUE; WL-TMRW_3MM
D4: GREEN; WL-TMRC_3MM
D5: YELLOW; WL-TMRC_3MM
J1: Conn_02x05_Odd_Even; 61201021621
J2: Conn_02x03_Odd_Even; 61200621621
PS1: TSR_1-2433E; CONV_TSR_1-2433E
R1: 0; R_Axial_DIN0207_L6.3mm_D2.5mm_P10.16mm_Horizontal
R2, R3, R4, R5: 220; R_Axial_DIN0617_L17.0mm_D6.0mm_P20.32mm_Horizontal
S1: 1543-650-149; 1543650149
U1: ESP32-S3-WROOM-1; ESP32-S3-WROOM-1U

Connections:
+3V3: C1.1, C3.1, C4.1, C5.1, D1.2 (A), D2.2 (A), D4.1 (K), D5.1, J1.1, J2.2, PS1.3 (+VOUT), R1.1, S1.2, U1.2 (3V3)
EN: J2.1, R1.2, U1.3 (EN)
GND: C1.2, C3.2, C4.2, C5.2, J1.3, J1.5, J1.7, J1.9, J2.4, PS1.2 (GND), S1.1, U1.1 (GND), U1.40 (GND), U1.41 (GND)
unnamed: D1.1 (K), R4.2
unnamed: D2.1 (K), R3.1
unnamed: D4.2 (A), R5.2
unnamed: D5.2, R2.2
unnamed: J1.2, U1.35 (MTMS/GPIO42)
unnamed: J1.4, U1.32 (MTCK/GPIO39/CLK_OUT3/SUBSPICS1)
unnamed: J1.6, U1.33 (MTDO/GPIO40/CLK_OUT2)
unnamed: J1.8, U1.34 (MTDI/GPIO41/CLK_OUT1)
unnamed: J2.3, U1.37 (U0TXD/GPIO43/CLK_OUT1)
unnamed: J2.5, U1.36 (U0RXD/GPIO44/CLK_OUT2)
unnamed: J2.6, U1.27 (GPIO0/BOOT)
unnamed: R2.1, U1.15 (GPIO3/TOUCH3/ADC1_CH2)
unnamed: R4.1, U1.23 (GPIO21)
unnamed: R5.1, U1.26 (GPIO45)
unnamed: R3.2, U1.16 (GPIO46)

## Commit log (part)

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2024-03-12 init
2024-03-12 add Files
2024-03-12 Add device.html in CMakeLists.txt
2024-04-16 schaltplan erstellt
2024-04-17 Schaltplan angepasst
2024-04-18 ESP32-S3 von der Espressif Library hinzugefügt und Schaltplan angepasst
2024-04-22 neue Bauteile hinzugefügt
2024-04-23 Anpassung der Leiterbahnen
2024-04-24 Backups gelöscht
2024-04-24 Anpassung von Bauelementen
2024-09-30 PCB überarbeitet
2024-09-30 Leiterbahnen editiert
2024-10-01 Alte Schaltpläne gelöscht und neue erstellt
2024-10-02 ESP32 Microcontroller geändert
2024-10-07 schaltplan überarbeitete
2024-12-03 6Pin header male hinzugefügt und Leiterbahnen optimiert
2024-12-03 Leiterbahnen überarbeitet
2024-12-12 microcontroller gewechselt und Layout angepasst
2025-03-04 usb-schnittstelle hinzugefügt
2026-01-27 Widerstand versetzt
2026-02-15 +3.3V Netzbezeichner hinzugefügt
2026-02-15 Entfernung der LED im Debugging Layout
2026-02-15 USB-Bridge entfernt. Globale Bezeichner USB+ und USB- hinzugefügt
2026-02-21 Steuerund der LEDs umgebaut
2026-02-23 Stückliste angefangen
2026-02-23 PDF generiert
2026-02-24 Wert vom Widerstand angepasst
2026-02-24 widerstände umplaziert
2026-04-06 AGENTS.md hinzugefügt
2026-06-05 v0.00.001 chore: Cursor Hooks und Pro-Prompt-Workflow-Rule projektlokal eingerichtet
    Übersetzt den Claude UserPromptSubmit-Hook als alwaysApply-Rule und sessionStart-Hook unter .cursor/.
2026-06-06 v0.00.001 fix: sessionStart-Hook auf PowerShell umgestellt
    Node ist in Cursors Hook-Umgebung unter Windows nicht im PATH; PowerShell-Skript liefert nun zuverlaessig additional_context.
